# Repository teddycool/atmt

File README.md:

# atmt
A project to create an autonomous toy monster truck

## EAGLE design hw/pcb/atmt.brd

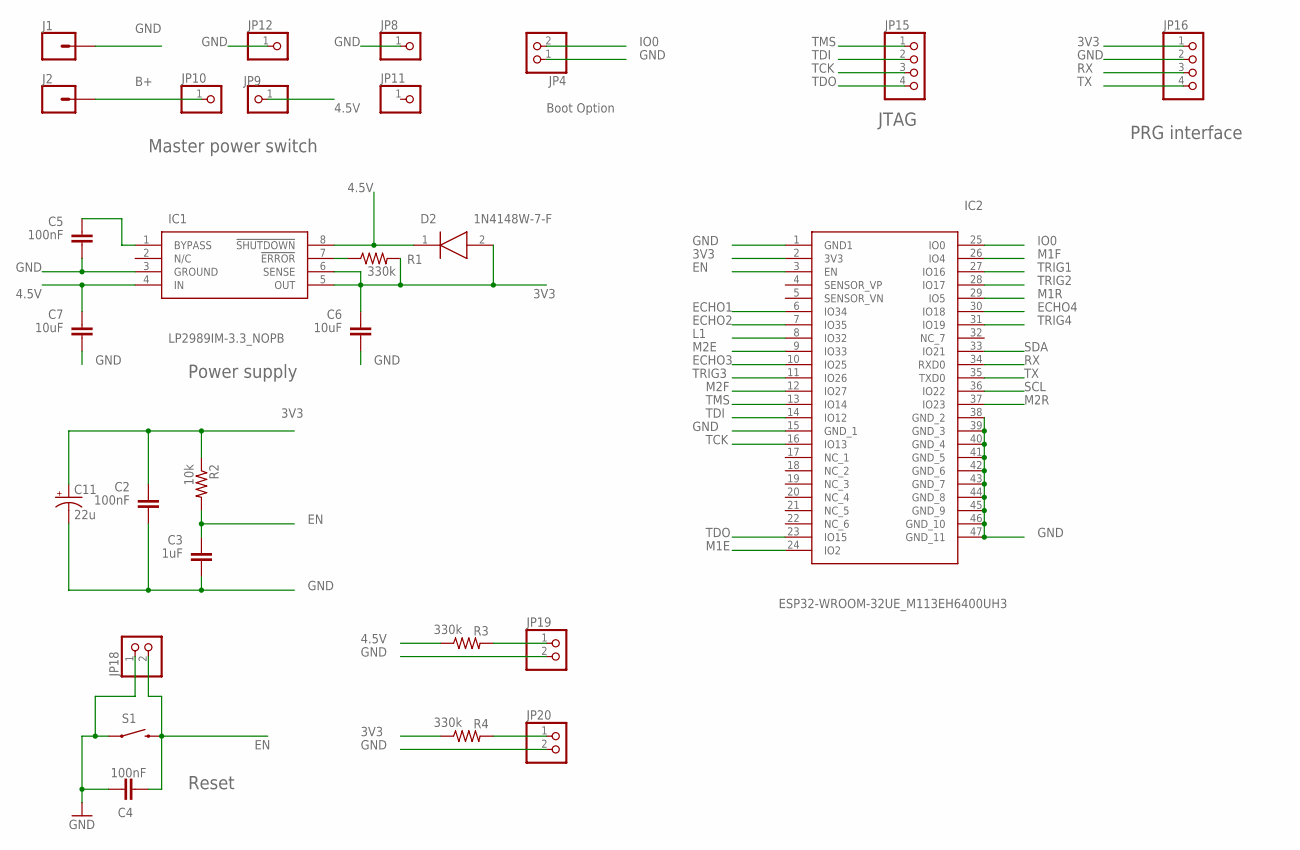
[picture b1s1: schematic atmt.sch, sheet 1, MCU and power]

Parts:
C2, C4, C5: 100nF; 0805
C3: 1uF; 0805
C6, C7: 10uF; 0805
C11: 22u; E2-5
D2: 1N4148W-7-F; SOD3716X115N
IC1: LP2989IM-3.3_NOPB; SOIC127P600X175-8N
IC2: ESP32-WROOM-32UE_M113EH6400UH3; ESP32WROOM32UEM113EH6400UH3Q0
J1, J2: CONN_01PTH_2MM; 1X01_2MM
JP4, JP18, JP19, JP20: PINHD-1X2; 1X02
JP8, JP9, JP10, JP11, JP12: PINHD-1X1; 1X01
JP15, JP16: PINHD-1X4; 1X04
R1, R3, R4: 330k; 0805
R2: 10k; 0805
S1: RESET; TACTILE-SWITCH-1101NE

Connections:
3V3: C2.1, C6.1, C11.+, D2.2 (A), IC1.5 (OUT), IC1.6 (SENSE), IC2.2 (3V3), JP16.1, R1.2, R2.1, R4.1; also elsewhere on the board
4.5V: C7.1, D2.1 (K), IC1.4 (IN), IC1.8 (!SHUTDOWN), JP9.1, R3.1; also elsewhere on the board
B+: J2.1, JP10.1
ECHO1: IC2.6 (IO34); also elsewhere on the board
ECHO2: IC2.7 (IO35); also elsewhere on the board
ECHO3: IC2.10 (IO25); also elsewhere on the board
ECHO4: IC2.30 (IO18); also elsewhere on the board
EN: C3.1, C4.2, IC2.3 (EN), JP18.2, R2.2, S1.2
GND: C2.2, C3.2, C4.1, C5.2, C6.2, C7.2, C11.-, IC1.3 (GROUND), IC2.1 (GND1), IC2.15 (GND_1), IC2.38 (GND_2), IC2.39 (GND_3), IC2.40 (GND_4), IC2.41 (GND_5), IC2.42 (GND_6), IC2.43 (GND_7), IC2.44 (GND_8), IC2.45 (GND_9), IC2.46 (GND_10), IC2.47 (GND_11), J1.1, JP4.1, JP8.1, JP12.1, JP16.2, JP18.1, JP19.2, JP20.2, S1.1; also elsewhere on the board
IO0: IC2.25 (IO0), JP4.2
L1: IC2.8 (IO32); also elsewhere on the board
M1E: IC2.24 (IO2); also elsewhere on the board
M1F: IC2.26 (IO4); also elsewhere on the board
M1R: IC2.29 (IO5); also elsewhere on the board
M2E: IC2.9 (IO33); also elsewhere on the board
M2F: IC2.12 (IO27); also elsewhere on the board
M2R: IC2.37 (IO23); also elsewhere on the board
unnamed: C5.1, IC1.1 (BYPASS)
unnamed: JP19.1, R3.2
unnamed: JP20.1, R4.2
unnamed: IC1.7 (!ERROR), R1.1
RX: IC2.34 (RXD0), JP16.3
SCL: IC2.36 (IO22); also elsewhere on the board
SDA: IC2.33 (IO21); also elsewhere on the board
TCK: IC2.16 (IO13), JP15.3
TDI: IC2.14 (IO12), JP15.2
TDO: IC2.23 (IO15), JP15.4
TMS: IC2.13 (IO14), JP15.1
TRIG1: IC2.27 (IO16); also elsewhere on the board
TRIG2: IC2.28 (IO17); also elsewhere on the board
TRIG3: IC2.11 (IO26); also elsewhere on the board
TRIG4: IC2.31 (IO19); also elsewhere on the board
TX: IC2.35 (TXD0), JP16.4

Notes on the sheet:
Boot Option
Reset
Power supply
Master power switch
JTAG
PRG interface

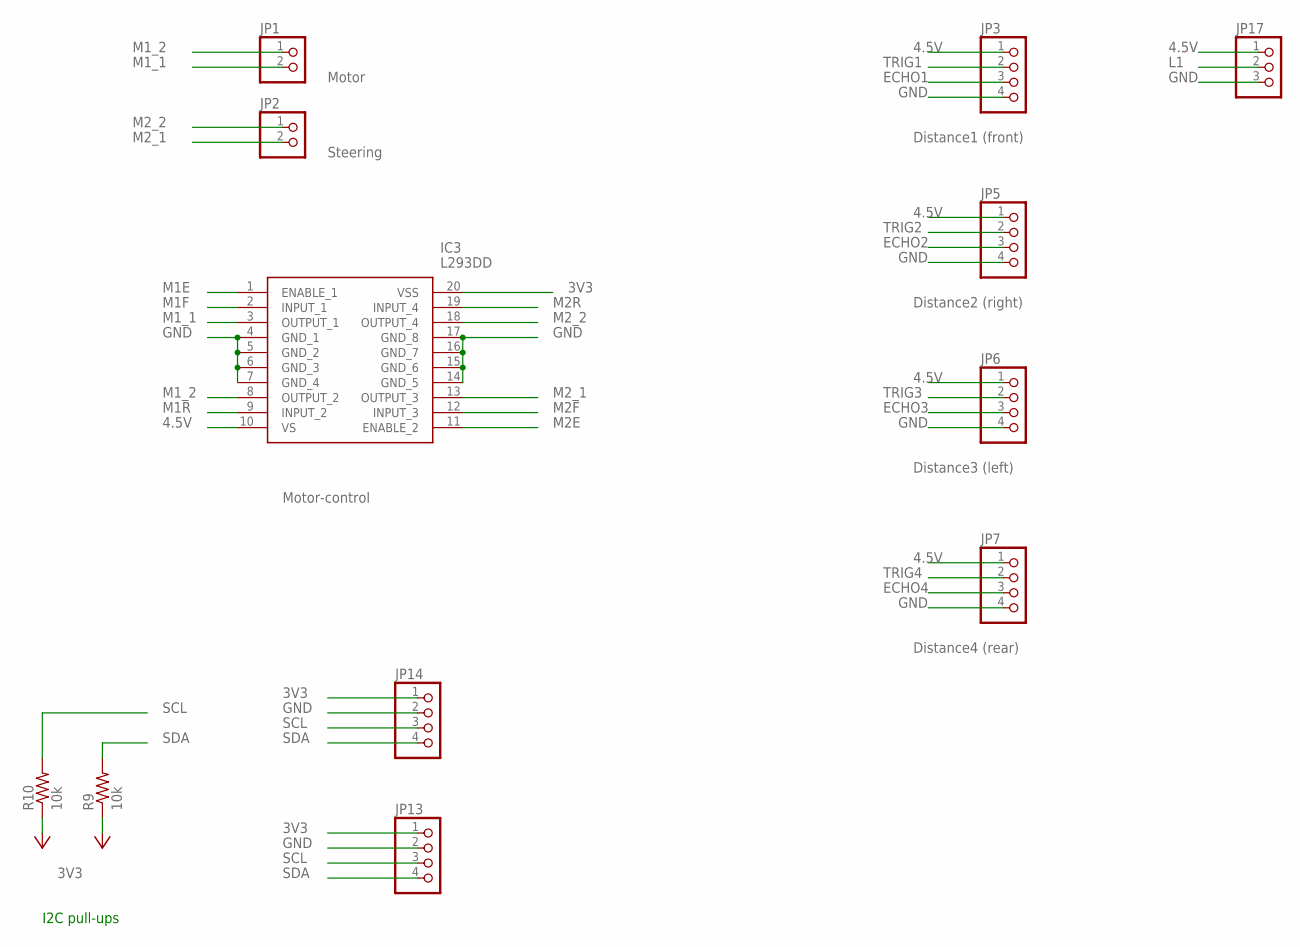
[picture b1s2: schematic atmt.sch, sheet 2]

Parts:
IC3: L293DD; SOIC127P1032X265-20N
JP1, JP2: PINHD-1X2/90; 1X02/90
JP3, JP5, JP6, JP7, JP13, JP14: PINHD-1X4; 1X04
JP17: PINHD-1X3; 1X03
R9, R10: 10k; 0805

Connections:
3V3: IC3.20 (VSS), JP13.1, JP14.1, R9.1, R10.1; also elsewhere on the board
4.5V: IC3.10 (VS), JP3.1, JP5.1, JP6.1, JP7.1, JP17.1; also elsewhere on the board
ECHO1: JP3.3; also elsewhere on the board
ECHO2: JP5.3; also elsewhere on the board
ECHO3: JP6.3; also elsewhere on the board
ECHO4: JP7.3; also elsewhere on the board
GND: IC3.4 (GND_1), IC3.5 (GND_2), IC3.6 (GND_3), IC3.7 (GND_4), IC3.14 (GND_5), IC3.15 (GND_6), IC3.16 (GND_7), IC3.17 (GND_8), JP3.4, JP5.4, JP6.4, JP7.4, JP13.2, JP14.2, JP17.3; also elsewhere on the board
L1: JP17.2; also elsewhere on the board
M1E: IC3.1 (ENABLE_1); also elsewhere on the board
M1F: IC3.2 (INPUT_1); also elsewhere on the board
M1R: IC3.9 (INPUT_2); also elsewhere on the board
M1_1: IC3.3 (OUTPUT_1), JP1.2
M1_2: IC3.8 (OUTPUT_2), JP1.1
M2E: IC3.11 (ENABLE_2); also elsewhere on the board
M2F: IC3.12 (INPUT_3); also elsewhere on the board
M2R: IC3.19 (INPUT_4); also elsewhere on the board
M2_1: IC3.13 (OUTPUT_3), JP2.2
M2_2: IC3.18 (OUTPUT_4), JP2.1
SCL: JP13.3, JP14.3, R10.2; also elsewhere on the board
SDA: JP13.4, JP14.4, R9.2; also elsewhere on the board
TRIG1: JP3.2; also elsewhere on the board
TRIG2: JP5.2; also elsewhere on the board
TRIG3: JP6.2; also elsewhere on the board
TRIG4: JP7.2; also elsewhere on the board

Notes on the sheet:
Motor
Steering
Distance1 (front)
Distance2 (right)
Distance3 (left)
Distance4 (rear)
Motor-control
I2C pull-ups

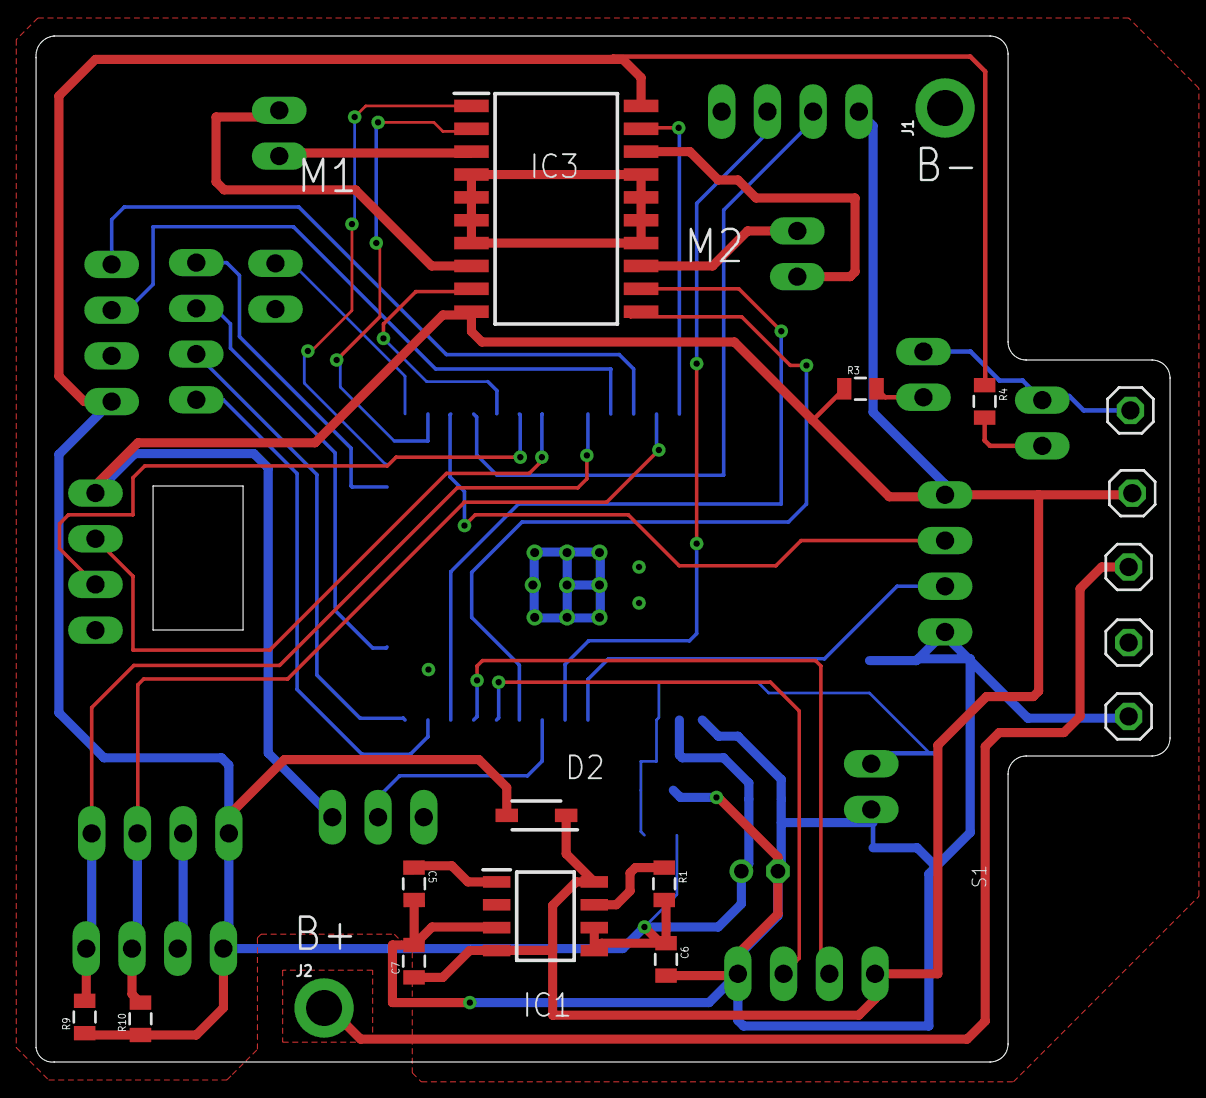
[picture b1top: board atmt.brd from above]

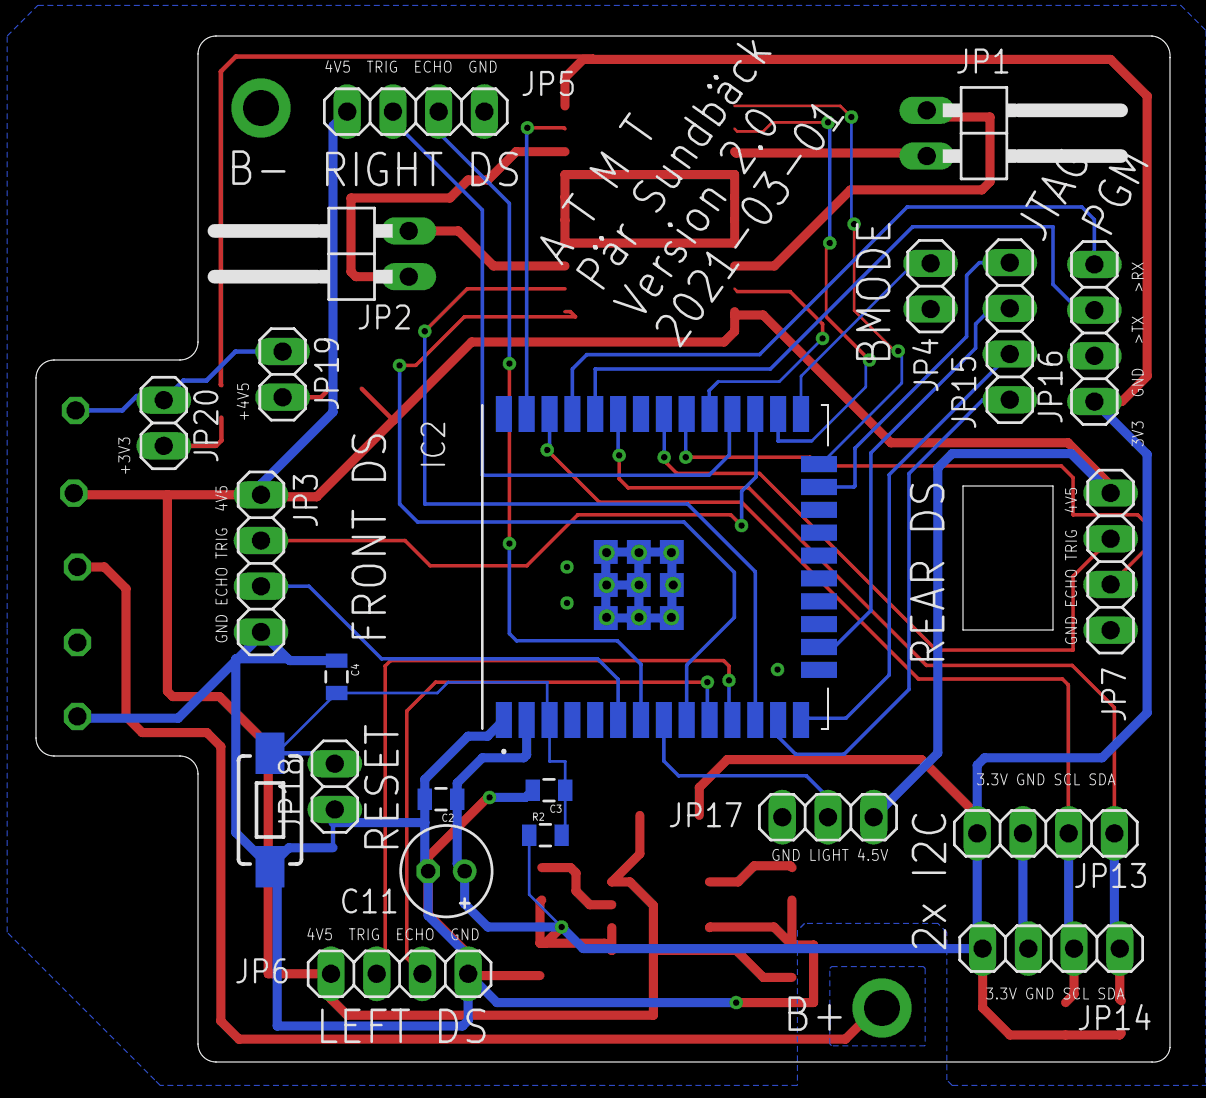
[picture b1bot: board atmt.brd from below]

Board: 2 copper layers, 63.0 x 57.0 mm, 40 parts (22 on the bottom side), 37 nets.

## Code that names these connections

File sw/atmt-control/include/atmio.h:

#ifndef ATMIO_H
#define ATMIO_H  



// Define pin-name and GPIO#. Pin # are depending on HW version
// Naming is FIXED

//Hardware version 2:
//-------------------

// Motor
#define M1E_PIN 2
#define M1F_PIN 4
#define M1R_PIN 5

// Steering
#define SENABLE 33
#define SRIGHT 27
#define SLEFT 23

// US sensors
#define TFRONT 16 // ECHO1
#define EFRONT 34
#define TLEFT 26 // ECHO3
#define ELEFT 25
#define TREAR 19 // ECHO4
#define EREAR 18
#define TRIGHT 17 // ECHO2
#define ERIGHT 35


#endif

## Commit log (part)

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2021-02-07 First filedrop
2021-02-07 added readme
2021-02-20 first commit of control-sysetm
2021-03-25 new board
2021-04-16 new pcb
2022-11-05 Updated after MiniHack
2024-04-13 First step for scaniahack
2024-04-28 Major update and clean-up
2024-05-04 Update and restructured...
2024-05-05 two tasks working
2024-05-05 typ fungerande version, dock men lite hårdkodat.... Var problem hitta rtos headerfiler så fick lägga till -I i platform.io
2024-05-05 Adapted to the toy truck for left and right sensor,
2024-05-05 stopped tracking many files
2024-05-08 Deleted old directories and files
2024-05-08 Logging and db-setup
2024-05-10 Now there should ONLY be my readme file (#3)
    * working version with flashing of leds from two tasks
    * two tasks working
    * typ fungerande version, dock men lite hårdkodat.... Var problem hitta rtos headerfiler så fick lägga till -I i platform.io
    * ok
    * ok test of pralell data from ultrasound
    * Adapted to the toy truck for left and right sensor,
2024-05-10 Testocode that includes safe read/write
2024-05-10 Added compass to dynamics and log to backend for all values
2024-05-12 Added a index.php file with a hellow world code and view_logs.php with the logic to visualize the logs
2024-05-13 Working example version for the truck, magnetic sensor part not testing as I do not have one
2024-05-13 Added a index.php file with a hellow world code and view_logs.php with the logic to visualize the logs (#7)
2024-05-16 Reversed order of logs to show latest on top
2024-05-16 Updated the index.php file from the rpi to the repo and added links from home to view logs and vise versa
2024-05-16 added a link to ota
2024-05-16 test
2024-05-16 strategy
2024-05-16 reverse back and forward
2024-05-16 strategy forward, backward, lights
2024-05-16 Statisc ip
2024-05-16 reverse when close
2024-05-16 reverse if something ahead
2024-05-16 forward if something behind
2024-05-16 ipadresser
2024-05-16 added mqtt measurement
2024-05-16 ip adresser take 3
2024-05-16 master strat
2024-05-16 Vehicle goes ztright based on gyro feedback (#11)
    * working version with flashing of leds from two tasks
    * two tasks working
    * typ fungerande version, dock men lite hårdkodat.... Var problem hitta rtos headerfiler så fick lägga till -I i platform.io
    * ok
    * ok test of pralell data from ultrasound
    * Adapted to the toy truck for left and right sensor,
2024-05-16 mqtt measurements shorter variable names
2024-05-16 added arduino json lib
2024-05-16 before nerge
2024-05-17 Get Mqtt messages but does loose many
2024-05-17 Removed postvalue function
2024-05-17 added agian iteration++ counter in the loop function
2024-05-17 cleaned some lines of code
2024-05-17 friday morning
2024-05-17 integrated sensor services
2024-05-17 changed delay(ms) function to Delay(vTaskDelay(pdMS_TO_TICKS(ms)))
2024-05-17 Added simple strategy without sensors
2024-05-17 not working
2024-05-17 invert steering when reverse
2024-05-17 Check if object on both sides
2024-05-28 Start of clean-up and restructure
2024-07-05 Before new branch
2025-01-31 First restruct
2025-01-31 Created a random foo file
2025-01-31 Scacaniahack 2024
2025-02-01 Updated docs
2025-02-01 AI generated example (not yet tested) as how to create different types of tasks.
2025-02-01 corrected the include paths
2025-02-01 Updated secrets and atmio definitions
2025-02-01 Examples directory started. (#22)
    * Scacaniahack 2024
    * AI generated example (not yet tested) as how to create different types of tasks.
    * corrected the include paths
    * calssing started. realised it will be very difficult to keep interrupts separate and to avoid the sensors disturb each other. So a redesign wioll be needed. COnstructor to create a table, then you 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
    ---------
2025-02-02 Restructure and new hw-test-sw
2025-02-07 Backup commit
2025-02-07 Usensor (#23)
    * Scacaniahack 2024
    * AI generated example (not yet tested) as how to create different types of tasks.
    * corrected the include paths
    * calssing started. realised it will be very difficult to keep interrupts separate and to avoid the sensors disturb each other. So a redesign wioll be needed. COnstructor to create a table, then you 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
    * Passing compilation for z_main_usensor for the first time. Linking problem, and not yet tested
    * Backup commit
2025-02-08 New kicad and a new hello-world-sw
2025-02-08 Seems to be working, Back sensor gives correct numbers, the other not, but could be cable problems (#24)
2025-02-08 First working new motor control. Only drive is implem,ented, breaking can be done later. Expect to use quite high number: 80-100 % for enough torque at 4-5 v.
2025-02-08 Removed a couple of defines that were not used.
2025-02-08 Docementation on how to build separate tests in platformio. First version.
2025-02-08 First working motor control with test pack that runs motor forward and backwards (#25)
    * Seems to be working, Back sensor gives correct numbers, the other not, but could be cable problems
    * First working new motor control. Only drive is implem,ented, breaking can be done later. Expect to use quite high number: 80-100 % for enough torque at 4-5 v.
    * Removed a couple of defines that were not used.
    * Docementation on how to build separate tests in platformio. First version.
    ---------
2025-02-08 First structure for the config package
2025-02-10 Unsensor (#26)
    * Seems to be working, Back sensor gives correct numbers, the other not, but could be cable problems
    * First working new motor control. Only drive is implem,ented, breaking can be done later. Expect to use quite high number: 80-100 % for enough torque at 4-5 v.
    * Removed a couple of defines that were not used.
    * Docementation on how to build separate tests in platformio. First version.
    * First structure for the config package
    * Higly improved Usensor, both the component test that shows both distance and age. And the comments and structure in the usensor class has been improved, especially around the POLL_INTERVAL
2025-02-10 Updated documents
2025-02-16 Logger and test_main
2025-02-16 Cleaned up and restructured a bit, preparing for different chassi-typesusing the same electronics
2025-02-22 New structure but still working as before
2025-02-23 MQTT step 1 and a telemetry-module
2025-03-01 Updated and tested usensor in accordance with the new directory structure
2025-03-01 updated platformio.ini (#27)
    * updated platformio.ini
    * Updated and tested usensor in accordance with the new directory structure
    ---------
2025-03-01 Added accsensor and all uodates required for that. It could be that the change of setget to long instead of int coaul case some issues with other packets, needs to be verified. maybe overlaying so th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
2025-03-01 Seems I missed these two for my accsensor commit.
2025-03-06 More to pull (#29)
    * updated platformio.ini
    * Updated and tested usensor in accordance with the new directory structure
    * Added accsensor and all uodates required for that. It could be that the change of setget to long instead of int coaul case some issues with other packets, needs to be verified. maybe overlaying so 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
    * Seems I missed these two for my accsensor commit.
    ---------
2025-03-08 First shot of kalman-filter for acc
2025-03-08 docs update
2025-03-08 First shot compass
2025-03-09 Fixed plattform.ini
2025-03-09 Accsensorcalibration added
2025-03-09 New steer, which lead to other modifications and improvements.... (#30)
    * Mainly recreation of steer, but some other updates were also required.
    * Accsensorcalibration added
    ---------
2025-03-09 z_main_steer_test file which initiates the setget before it is used by steer.
2025-03-09 Corrected the PWM channel since the motor package need booth ch0 and ch 1 when using differential steering.
2025-03-09 added so that both proportional sterring as well as the original digital steering is tested.
2025-03-10 Uppdates ragerding steering, should now support ordinary motor and not only servo (#31)
    * Updated needed files to support so that steer.direction stores the latest steering number in the globalVar steerDirection. This is so that motor:drive can read and use this information if different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
    * z_main_steer_test file which initiates the setget before it is used by steer.
    * Corrected the PWM channel since the motor package need booth ch0 and ch 1 when using differential steering.
    * Added support for the normal motor instead of a servo for steering.
    * added so that both proportional sterring as well as the original digital steering is tested
2025-03-10 old header files in old location. Needs to be removed to avoid confusion
2025-03-11 added missing ref to config.cpp for env:motor
2025-03-15 Hardware test program
2025-03-17 gy271
2025-03-17 expander working basic
2025-03-17 differential basic support added to motor
2025-03-17 simple i2c scanner to find unknown addresses
2025-03-18 Some updates
2025-03-18 merging into main
2025-03-18 merged from upstream with my code
2025-03-18 corrected default config to be SINGLE motor and MOTOR steering.
2025-03-18 Localdev
2025-03-18 Minor fixes to get motor and steer to build agan. Had to remove strange lib dependency I dfo not have and packages do not need. In steer the use of the calculated variables and the correct calls to l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
2025-03-20 Added ESP32 ID of JCA01 to config file
2025-03-20 Remove .vscode directory from Git tracking
2025-03-20 Sensor-values in structure, motor stops when clesd to obstacle
2025-03-20 remove vscode
2025-03-20 Simple bash remote control client via mqtt.
2025-03-20 Now with minimum delay in MQTT messaging
2025-03-20 Added remote bash client with new jeson format with 10 degrees precision for steering
2025-03-20 Added yolo script for video detection
2025-03-21 Changed the detection script to detect only cup, bottle, toothbrush, apple and cellphone
2025-03-21 added detection for moving forward and stop using yolo
2025-03-21 Remote-controls
2025-03-21 added requirements and README.md file to bash_remote_control
2025-03-21 moved remote.sh script and detection_script.py to remote directory
2025-03-22 motor reworked as well as config and setget. All to make packages more consistant, remove the unpredictable class instantiations and instead use regular function calls.
2025-03-23 Added options to remote.sh to be able to choose VEHICLE_ID and MQTT broker as arguments to the command line. Added a Usage description. If no option is given, it runs with the default ones from the S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
2026-02-21 Status before scaniahack 2026
2026-02-21 Add comprehensive .gitignore for embedded development project
    - PlatformIO build artifacts and IDE files
    - Python virtual environments and bytecode
    - KiCad backup and temporary files
    - FreeCAD backup files
    - OS and IDE temporary files
    - Security-sensitive files (secrets.h, config files)
2026-03-16 Before cleanup for ScaniaHack-2026
2026-03-16 Removed unused code and files
2026-03-16 Rename: sw -> EmbeddedSw - Update VS Code configs and documentation
2026-03-16 Huge restructure forScaniaHack 2026
2026-03-19 Before
2026-03-19 Added config
2026-03-19 added truck simulator and added gitignore for avoid adding venv to git
2026-03-19 refactored the code to have a more modular way of putting an explore strategy
2026-03-19 changed the truck simulation code to start at a random place and to send the data every second.
2026-03-19 Changed the view of the map visualizer to plot every sensor separately
2026-03-19 Fixed crack/reboot and motorparameters
2026-03-19 Visualization of the truck_simulator is working good, but not the strategy
2026-03-19 Added embedded control that simulated the explore logic in the embedded system. It is working well.
2026-03-19 added json structure into the guardrails
2026-03-19 added drift to the streight drive in the truck simulator, added rdp to get the final map to the map visualizator
2026-03-19 changed to L shape for the simulator
2026-03-19 New json
2026-03-20 added a new simulator and room mapper, also added a truck_remote script that implements different exploration strategies
2026-03-20 changed the direction stength to 60 in remote

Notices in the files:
parts and their libraries:
SparkFun-Connectors: Licensing: Creative Commons ShareAlike 4.0 International - https://creativecommons.org/licenses/by-sa/4.0
